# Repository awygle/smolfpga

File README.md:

# smolfpga

`smolfpga` is a development board for the Lattice ice40 LM series of FPGAs. Its primary purpose in life is to facilitate the development of support for the LM family in the [icestorm toolchain](http://www.clifford.at/icestorm/).

`smolfpga` is heavily inspired by the [TinyFPGA](http://tinyfpga.com/) series of boards by Luke Valenty (@tinyfpga), and some of the footprints and schematic symbols used in this project were borrowed from the TinyFPGA B2 board under the GPLv3.

Apologies to @whitequark for borrowing the 'smol' from [smoltcp](https://github.com/m-labs/smoltcp) - I am very bad at naming things.

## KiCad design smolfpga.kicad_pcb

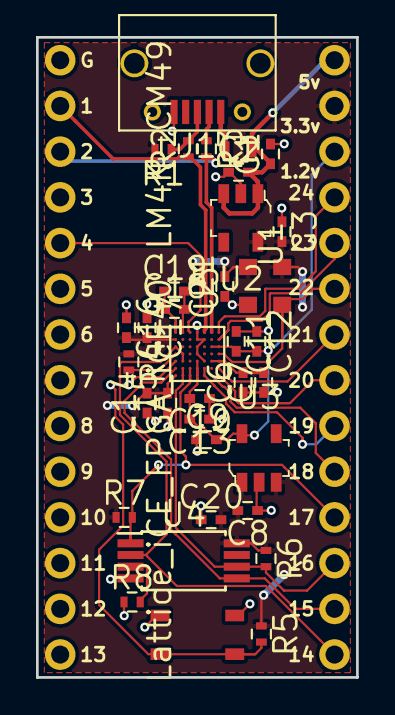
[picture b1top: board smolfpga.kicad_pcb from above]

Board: 2 copper layers, 17.8 x 35.6 mm, 37 parts (0 on the bottom side), 26 nets.

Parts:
C1: 10uF; C_0402
C2, C3, C8, C9: 1uF; C_0402
C6, C10, C12, C20, C21: 100nF; C_0402
C7, C11, C13: 10nF; C_0402
C14, C15, C16, C17, C18, C19: C; C_0402
J1: USB_B_Micro; USB_Micro-B
J2, J3: Conn_01x14; Pin_Header_Straight_1x14_Pitch2.54mm
L1: Ferrite_Bead_Small; L_0603
R1: 1K5; R_0402
R2, R3: 68; R_0402
R4, R5: R; R_0402
R6, R7, R8: 10K; R_0402
SW1: SW_Push; PTS_810_SMT_Switch
U1: Lattice_iCE_FPGA_iCE40-LM4K-CM49; VFBGA-49
U2: LP5907MFX-3_3_NOPB; SOT-753
U3: LP5907MFX-1_2_NOPB; SOT-753
U4: AT25SF041-XMHD-T; TSSOP-8_4.4x3mm_Pitch0.65mm
U5: DSC6001CI2A-016.0000T; CDFN3225-4LD-PL-1

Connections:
+1V2: C9.2, C10.2, C11.2, C12.2, C13.2, J2.3, U1.A3, U1.B3, U1.D5, U1.D6, U1.D7, U3.5
+3V3: C3.2, C6.2, C7.2, C8.2, C14.2, C15.2, C16.2, C17.2, C20.2, C21.2, J2.2, R1.2, R4.1, R5.1, R6.1, R7.1, U1.A5, U1.B5, U1.G2, U1.G7, U2.5, U3.1, U3.3, U4.8, U5.1, U5.4
+5V: C1.1, C2.2, J2.1, L1.1, U2.1, U2.3
A1: J2.4, U1.A1
A2: J2.5, U1.A2
A4: J2.6, U1.A4, U5.3
A6: J2.7, U1.A6
A7: J2.8, U1.A7
B1: J3.3, R3.2, U1.B1
B7: J2.10, U1.B7
C1: J3.2, R2.1, U1.C1
C6: J2.9, U1.C6, U1.C7
CS_B: J2.11, R7.2, U1.E6, U1.E7, U4.1
E1: J3.5, U1.E1
GND: C1.2, C2.1, C3.1, C6.1, C7.1, C8.1, C9.1, C10.1, C11.1, C12.1, C13.1, C14.1, C15.1, C16.1, C17.1, C20.1, C21.1, J1.5, J1.6, J3.1, R8.1, SW1.1, U1.C2, U1.C5, U1.D1, U1.D2, U1.D3, U1.D4, U2.2, U3.2, U4.4, U5.2
GNDPLL: C18.1, C19.1, U1.G1
unnamed: C18.2, C19.2, U1.F1
unnamed: J1.1, L1.2
unnamed: J1.2, R3.1
unnamed: J1.3, R1.1, R2.2
unnamed: R4.2, U1.G4
unnamed: R8.2, U4.3
RESET_B: R5.2, SW1.2, U1.G5
SCK: J2.12, R6.2, U1.F6, U1.F7, U4.6
SI: J2.13, U1.G6, U4.5
SO: J2.14, U1.F4, U1.F5, U1.G3, U4.2

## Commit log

2018-04-01 Design files commit.
2018-04-05 Added additional required files, fabrication outputs, BOM, and schematic PDF.
